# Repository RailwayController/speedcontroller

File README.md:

<!--
SPDX-FileCopyrightText: 2022 Sidings Media <contact@sidingsmedia.com>
SPDX-License-Identifier: CC-BY-SA-4.0
-->

# Railway Controller - Speed controller

The speed control board is one of the most important control nodes in the
railway controller system as it is responsible for powering the trains in use.

The board is based upon the ATtiny84 and makes use of the DRV8872 motor driver
IC. A small amount of protection circuitry to protect against large over
voltages on the motor lines has been included. The board is designed to fit
inside a standard 3U eurocard enclosure with a depth of 160mm and a height of
100mm. The rear connector provides connectivity to the backplane to allow
communication between all nodes in the rack as well as to supply power to the
board.

The PCBs have been designed with 2 layers and with SMD components that should be
possible to hand solder with a small tip and some practice. An important note,
the boards have been designed acording to JLCPCB's design constraints, if you
are ordering from a different manufacturer, it is a good idea to make sure that
they support the same or better constraints.

This repository contains designs for the speed control board for
use with the railway controller system. Rendered versions of the schematics, for
example schematics in the PDF format, are included with the releases. Gerber
files are also included with releases. These have been generated to work with
JLCPCB but they should work with most other board manufacturers. 

## Licence
This repo uses the [REUSE](https://reuse.software) standard in order to
communicate the correct licence for the file. For those unfamiliar with
the standard the licence for each file can be found in one of three
places. The licence will either be in a comment block at the top of the
file, in a `.license` file with the same name as the file, or in the
dep5 file located in the `.reuse` directory. If you are unsure of the
licencing terms please contact
[contact@sidingsmedia.com](mailto:contact@sidingsmedia.com?subject=Railway%20Controller%20Licence).
All files committed to this repo must contain valid licencing
information or the pull request can not be accepted.

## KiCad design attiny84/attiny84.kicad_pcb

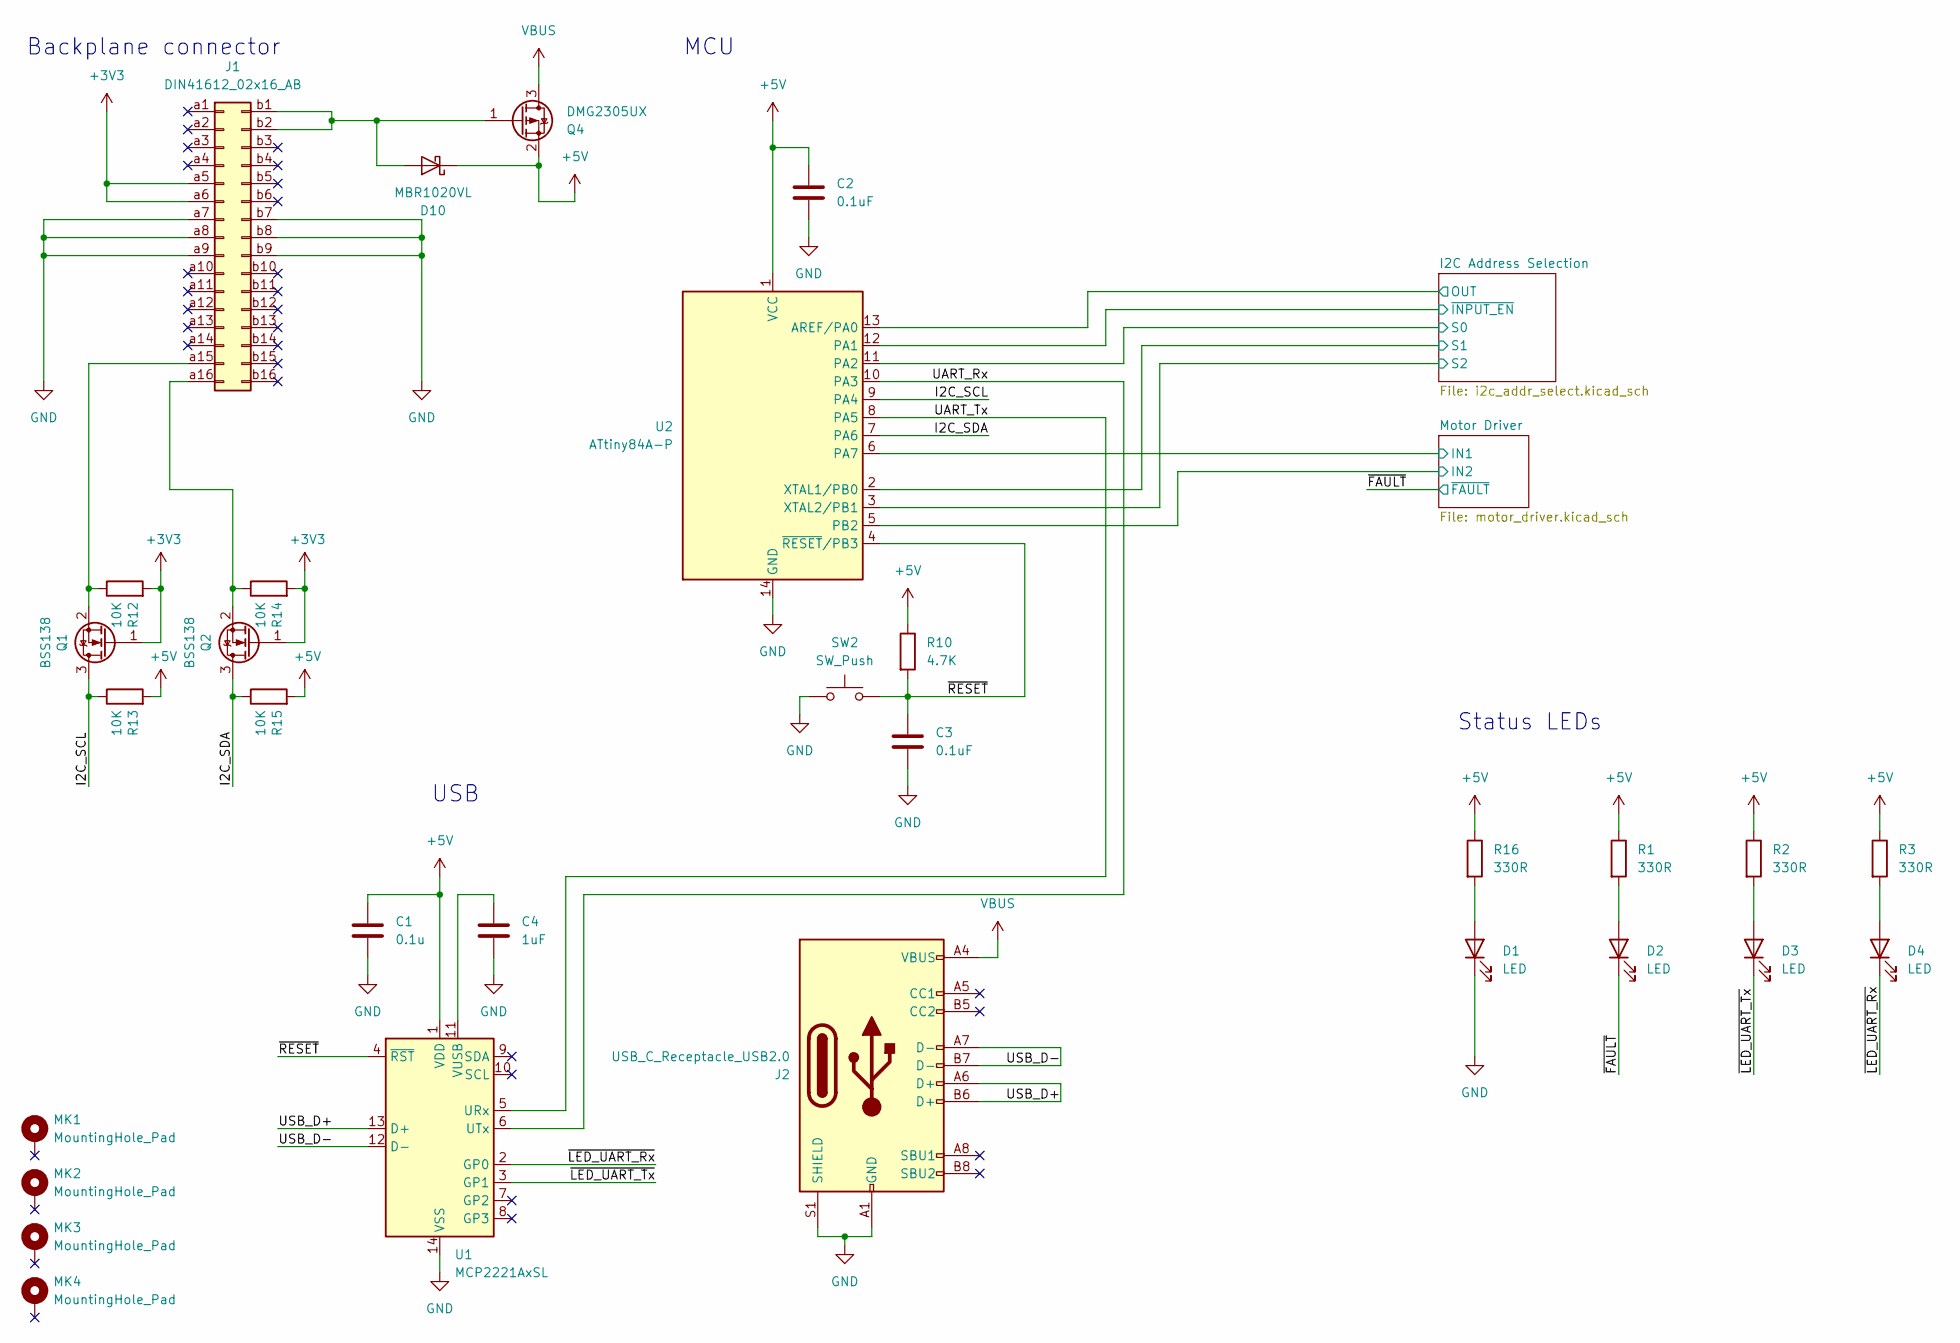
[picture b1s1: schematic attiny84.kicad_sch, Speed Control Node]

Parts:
C1: 0.1u; C_1206_3216Metric_Pad1.33x1.80mm_HandSolder
C2, C3: 0.1uF; C_1206_3216Metric_Pad1.33x1.80mm_HandSolder
C4: 1uF; C_1206_3216Metric_Pad1.33x1.80mm_HandSolder
D1, D2, D3, D4: LED; C_0402_1005Metric_Pad0.74x0.62mm_HandSolder
D10: MBR1020VL; D_SOD-123F
J1: DIN41612_02x16_AB; DIN41612_B2_2x16_Male_Horizontal_THT
J2: USB_C_Receptacle_USB2.0; USB_C_Receptacle_Palconn_UTC16-G
MK1, MK2, MK3, MK4: MountingHole_Pad; MountingHole_2.7mm
Q1, Q2: BSS138; SOT-23
Q4: DMG2305UX; SOT-23
R1, R2, R3, R16: 330R; R_1206_3216Metric_Pad1.30x1.75mm_HandSolder
R10: 4.7K; R_1206_3216Metric_Pad1.30x1.75mm_HandSolder
R12, R13, R14, R15: 10K; R_1206_3216Metric_Pad1.30x1.75mm_HandSolder
SW2: SW_Push; SW_SPST_B3U-1000P
U1: MCP2221AxSL; SOIC-14_3.9x8.7mm_P1.27mm
U2: ATtiny84A-P; SOIC-14_3.9x8.7mm_P1.27mm

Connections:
+3V3: J1.a5, J1.a6, Q1.1 (G), Q2.1 (G), R12.2, R14.2
+5V: C1.1, C2.1, D10.1 (K), Q4.2 (S), R1.1, R2.1, R3.1, R10.1, R13.2, R15.2, R16.1, U1.1 (VDD), U2.1 (VCC); also elsewhere on the board
/I2C Address Selection/OUT: U2.13 (AREF/PA0); also elsewhere on the board
/I2C Address Selection/S0: U2.11 (PA2); also elsewhere on the board
/I2C Address Selection/S1: U2.2 (XTAL1/PB0); also elsewhere on the board
/I2C Address Selection/S2: U2.3 (XTAL2/PB1); also elsewhere on the board
/I2C Address Selection/~INPUT_EN: U2.12 (PA1); also elsewhere on the board
/I2C_SCL: Q1.3 (D), R13.1, U2.9 (PA4)
/I2C_SDA: Q2.3 (D), R15.1, U2.7 (PA6)
/Motor Driver/IN1: U2.6 (PA7); also elsewhere on the board
/Motor Driver/IN2: U2.5 (PB2); also elsewhere on the board
/UART_Rx: U1.6 (UTx), U2.10 (PA3)
/UART_Tx: U1.5 (URx), U2.8 (PA5)
/USB_D+: J2.A6 (D+), J2.B6 (D+), U1.13 (D+)
/USB_D-: J2.A7 (D-), J2.B7 (D-), U1.12 (D-)
/~FAULT: D2.1 (K); also elsewhere on the board
/~LED_UART_Rx: D4.1 (K), U1.2 (GP0)
/~LED_UART_Tx: D3.1 (K), U1.3 (GP1)
/~RESET: C3.1, R10.2, SW2.2, U1.4 (~RST), U2.4 (~RESET/PB3)
GND: C1.2, C2.2, C3.2, C4.2, D1.1 (K), J1.a7, J1.a8, J1.a9, J1.b7, J1.b8, J1.b9, J2.A1 (GND), J2.A12 (GND), J2.B1 (GND), J2.B12 (GND), J2.S1 (SHIELD), SW2.1, U1.14 (VSS), U2.14 (GND); also elsewhere on the board
unnamed: C4.1, U1.11 (VUSB)
unnamed: D1.2 (A), R16.2
unnamed: D2.2 (A), R1.2
unnamed: D3.2 (A), R2.2
unnamed: D4.2 (A), R3.2
unnamed: D10.2 (A), J1.b1, J1.b2, Q4.1 (G)
unnamed: J1.a15, Q1.2 (S), R12.1
unnamed: J1.a16, Q2.2 (S), R14.1
VBUS: J2.A4 (VBUS), J2.A9 (VBUS), J2.B4 (VBUS), J2.B9 (VBUS), Q4.3 (D)

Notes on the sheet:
MCU
Backplane connector
Status LEDs
USB

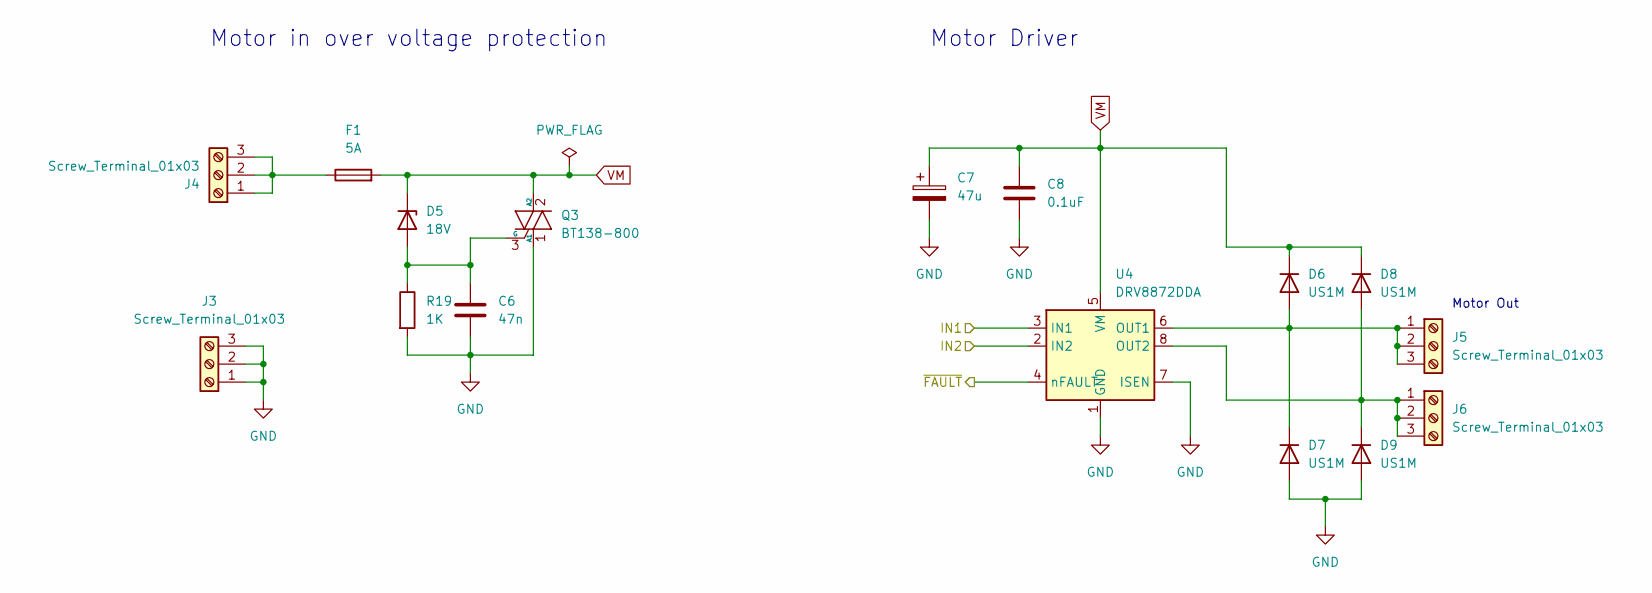
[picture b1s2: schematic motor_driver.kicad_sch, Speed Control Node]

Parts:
C6: 47n; C_1206_3216Metric_Pad1.33x1.80mm_HandSolder
C7: 47u; CP_Elec_6.3x5.7
C8: 0.1uF; C_1206_3216Metric_Pad1.33x1.80mm_HandSolder
D5: 18V; D_SOD-123F
D6, D7, D8, D9: US1M; D_SMA
F1: 5A; Fuseholder_Littelfuse_445_030_series_5x20mm
J3, J4, J5, J6: Screw_Terminal_01x03; TerminalBlock_bornier-3_P5.08mm
Q3: BT138-800; TO-220-3_Vertical
R19: 1K; R_1206_3216Metric_Pad1.30x1.75mm_HandSolder
U4: DRV8872DDA; Texas_HTSOP-8-1EP_3.9x4.9mm_P1.27mm_EP2.95x4.9mm_Mask2.4x3.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

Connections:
/Motor Driver/IN1: U4.3 (IN1); also elsewhere on the board
/Motor Driver/IN2: U4.2 (IN2); also elsewhere on the board
/~FAULT: U4.4 (nFAULT); also elsewhere on the board
GND: C6.2, C7.2, C8.2, D7.2 (A), D9.2 (A), J3.1, J3.2, J3.3, Q3.1 (A1), R19.2, U4.1 (GND), U4.7 (ISEN), U4.9 (GND); also elsewhere on the board
unnamed: C6.1, D5.2 (A), Q3.3 (G), R19.1
unnamed: D6.2 (A), D7.1 (K), J5.1, J5.2, J5.3, U4.6 (OUT1)
unnamed: D8.2 (A), D9.1 (K), J6.1, J6.2, J6.3, U4.8 (OUT2)
unnamed: F1.1, J4.1, J4.2, J4.3
VM: C7.1, C8.1, D5.1 (K), D6.1 (K), D8.1 (K), F1.2, Q3.2 (A2), U4.5 (VM)

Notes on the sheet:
Motor Driver
Motor Out
Motor in over voltage protection

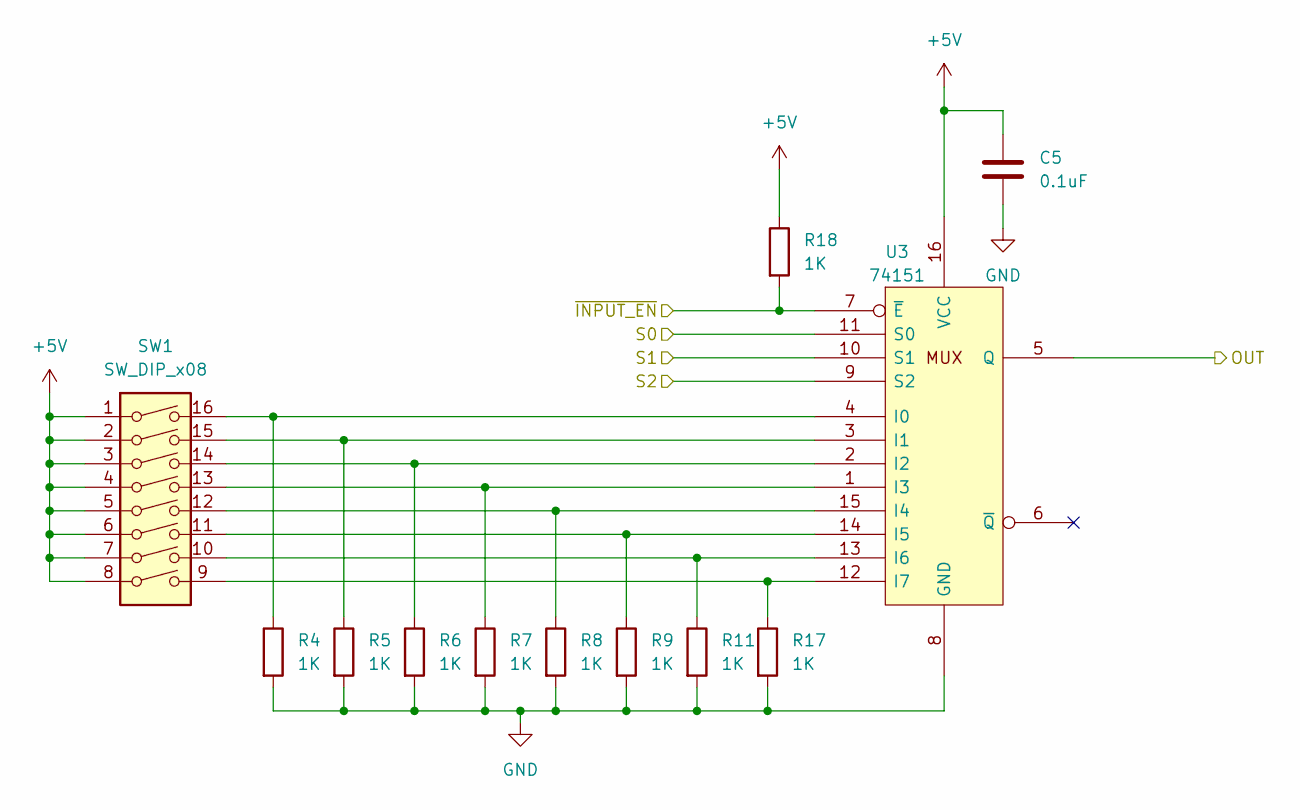
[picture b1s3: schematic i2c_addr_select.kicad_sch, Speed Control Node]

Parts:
C5: 0.1uF; C_1206_3216Metric_Pad1.33x1.80mm_HandSolder
R4, R5, R6, R7, R8, R9, R11, R17, R18: 1K; R_1206_3216Metric_Pad1.30x1.75mm_HandSolder
SW1: SW_DIP_x08; SW_DIP_SPSTx08_Slide_6.7x21.88mm_W7.62mm_P2.54mm_LowProfile
U3: 74151; SOIC-16_3.9x9.9mm_P1.27mm

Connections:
+5V: C5.1, R18.1, SW1.1, SW1.2, SW1.3, SW1.4, SW1.5, SW1.6, SW1.7, SW1.8, U3.16 (VCC); also elsewhere on the board
/I2C Address Selection/OUT: U3.5 (Q); also elsewhere on the board
/I2C Address Selection/S0: U3.11 (S0); also elsewhere on the board
/I2C Address Selection/S1: U3.10 (S1); also elsewhere on the board
/I2C Address Selection/S2: U3.9 (S2); also elsewhere on the board
/I2C Address Selection/~INPUT_EN: R18.2, U3.7 (~E); also elsewhere on the board
GND: C5.2, R4.2, R5.2, R6.2, R7.2, R8.2, R9.2, R11.2, R17.2, U3.8 (GND); also elsewhere on the board
unnamed: R4.1, SW1.16, U3.4 (I0)
unnamed: R5.1, SW1.15, U3.3 (I1)
unnamed: R6.1, SW1.14, U3.2 (I2)
unnamed: R7.1, SW1.13, U3.1 (I3)
unnamed: R8.1, SW1.12, U3.15 (I4)
unnamed: R9.1, SW1.11, U3.14 (I5)
unnamed: R11.1, SW1.10, U3.13 (I6)
unnamed: R17.1, SW1.9, U3.12 (I7)

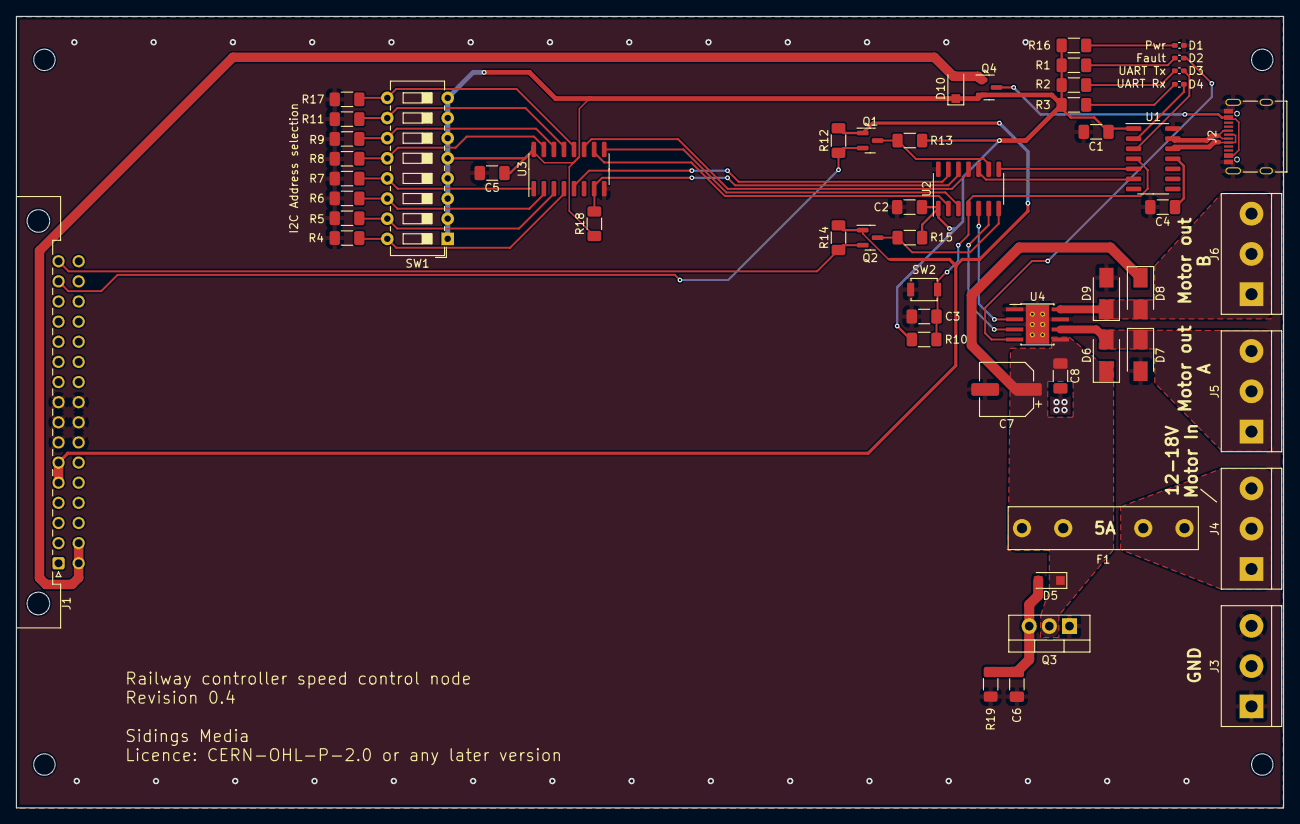
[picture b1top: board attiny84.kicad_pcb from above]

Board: 2 copper layers, 159.9 x 99.9 mm, 58 parts (0 on the bottom side), 42 nets.

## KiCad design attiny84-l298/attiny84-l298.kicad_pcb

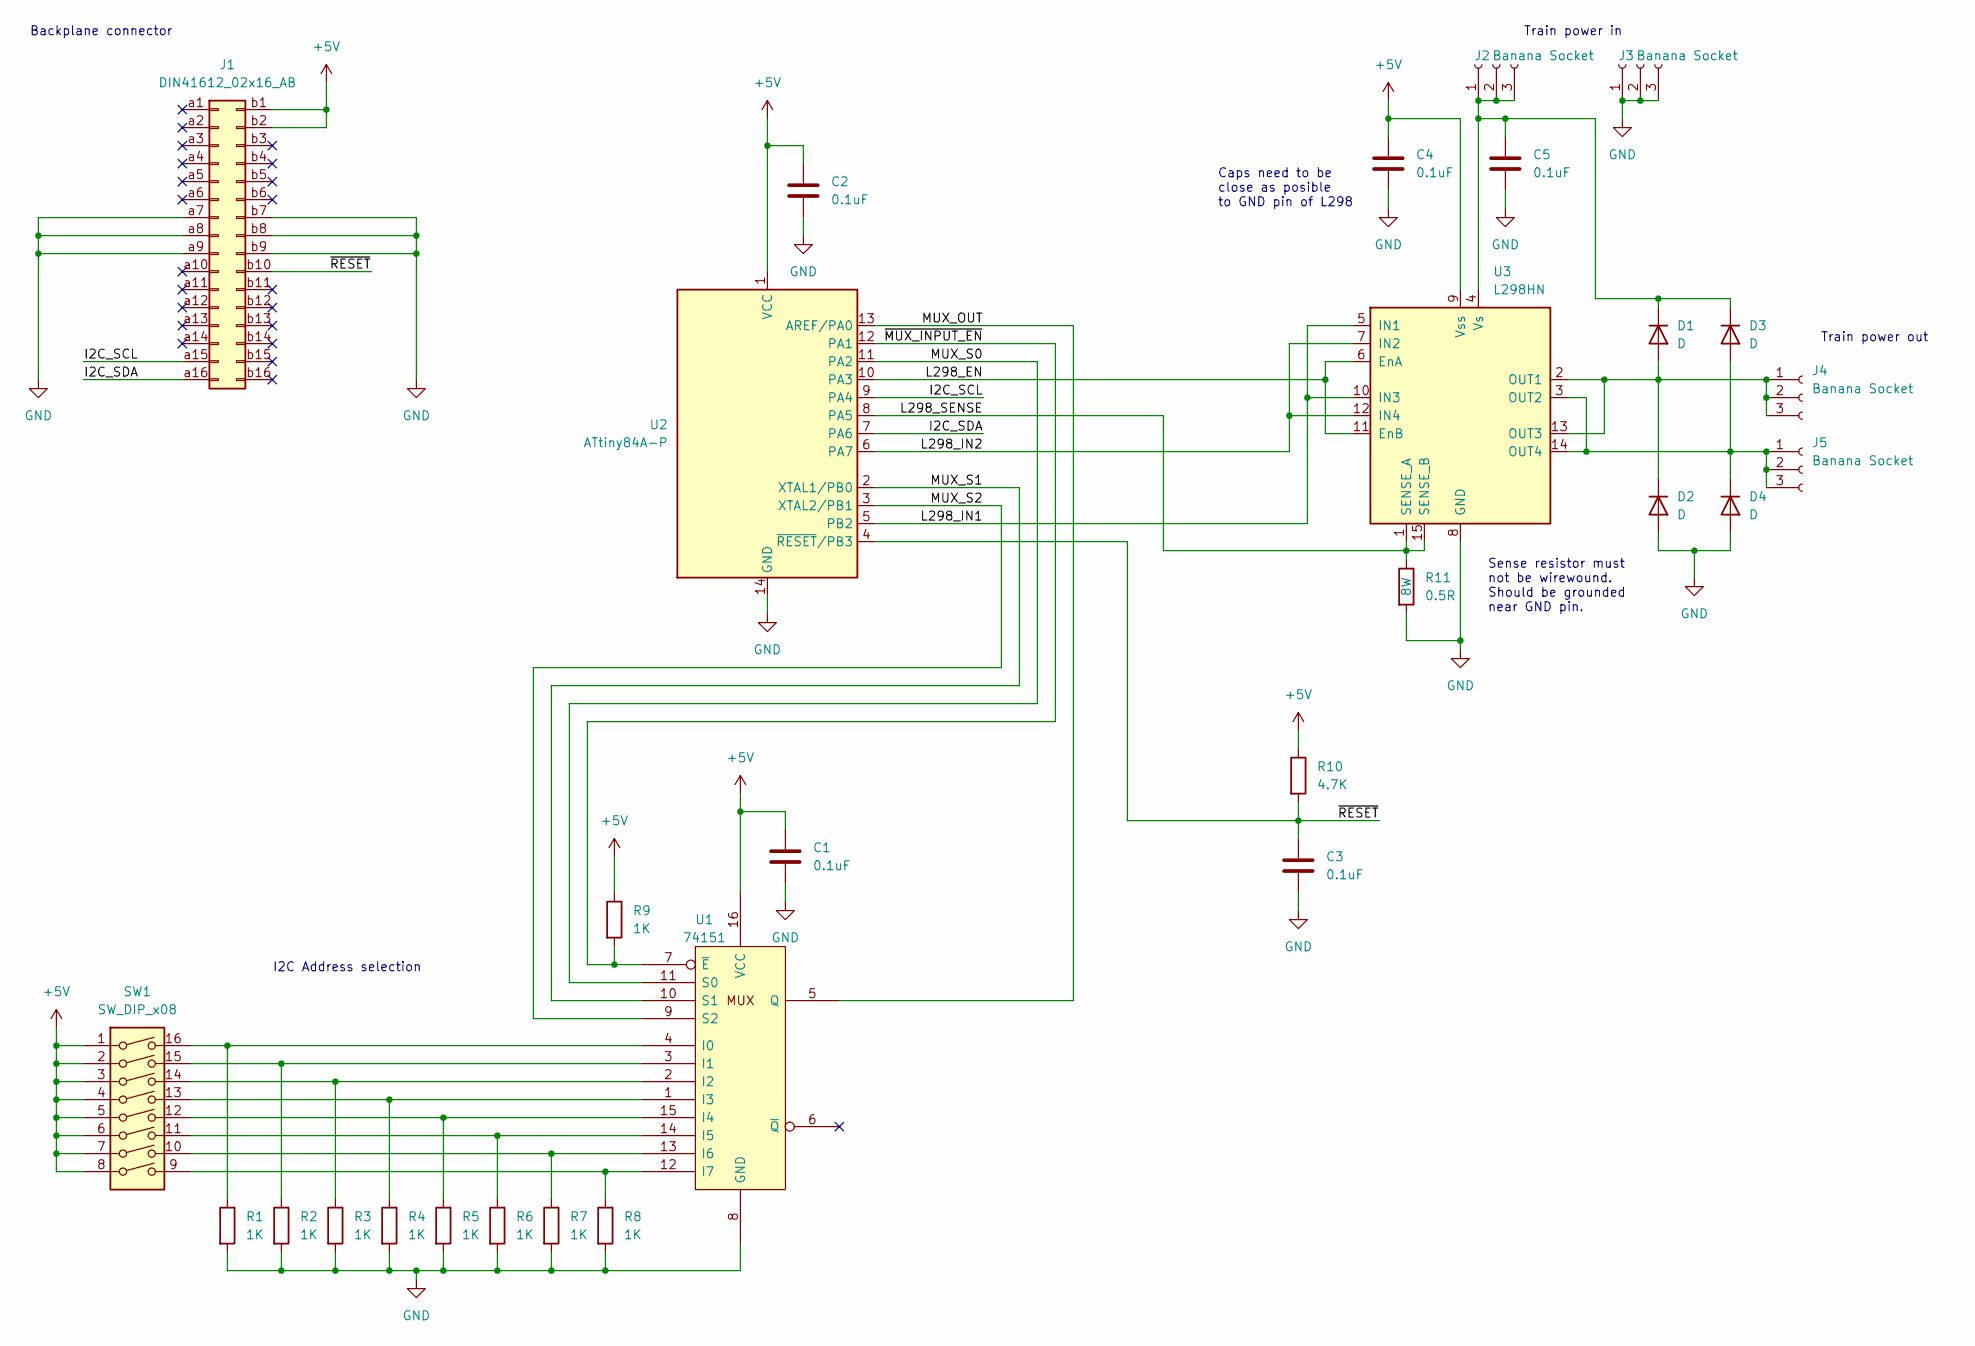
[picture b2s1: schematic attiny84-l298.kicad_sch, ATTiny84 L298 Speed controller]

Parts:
C1, C2, C3, C4, C5: 0.1uF; C_Disc_D4.7mm_W2.5mm_P5.00mm
D1, D2, D3, D4: D; D_5W_P10.16mm_Horizontal
J1: DIN41612_02x16_AB; DIN41612_B2_2x16_Male_Horizontal_THT
J2, J3, J4, J5: Banana Socket; Banana_Jack_3Pin
R1, R2, R3, R4, R5, R6, R7, R8, R9: 1K; R_Axial_DIN0207_L6.3mm_D2.5mm_P7.62mm_Horizontal
R10: 4.7K; R_Axial_DIN0207_L6.3mm_D2.5mm_P7.62mm_Horizontal
R11: 0.5R; R_Axial_DIN0617_L17.0mm_D6.0mm_P20.32mm_Horizontal
SW1: SW_DIP_x08; DIP-16_W7.62mm
U1: 74151; DIP-16_W7.62mm
U2: ATtiny84A-P; DIP-14_W7.62mm
U3: L298HN; TO-220-15_P2.54x2.54mm_StaggerOdd_Lead5.84mm_TabDown

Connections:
+5V: C1.1, C2.1, C4.1, J1.b1, J1.b2, R9.1, R10.1, SW1.1, SW1.2, SW1.3, SW1.4, SW1.5, SW1.6, SW1.7, SW1.8, U1.16 (VCC), U2.1 (VCC), U3.9 (Vss)
/I2C_SCL: J1.a15, U2.9 (PA4)
/I2C_SDA: J1.a16, U2.7 (PA6)
/L298_EN: U2.10 (PA3), U3.6 (EnA), U3.11 (EnB)
/L298_IN1: U2.5 (PB2), U3.5 (IN1), U3.10 (IN3)
/L298_IN2: U2.6 (PA7), U3.7 (IN2), U3.12 (IN4)
/L298_SENSE: R11.1, U2.8 (PA5), U3.1 (SENSE_A), U3.15 (SENSE_B)
/MUX_OUT: U1.5 (Q), U2.13 (AREF/PA0)
/MUX_S0: U1.11 (S0), U2.11 (PA2)
/MUX_S1: U1.10 (S1), U2.2 (XTAL1/PB0)
/MUX_S2: U1.9 (S2), U2.3 (XTAL2/PB1)
/~MUX_INPUT_EN: R9.2, U1.7 (~E), U2.12 (PA1)
/~RESET: C3.1, J1.b10, R10.2, U2.4 (~RESET/PB3)
GND: C1.2, C2.2, C3.2, C4.2, C5.2, D2.2 (A), D4.2 (A), J1.a7, J1.a8, J1.a9, J1.b7, J1.b8, J1.b9, J3.1, J3.2, J3.3, R1.2, R2.2, R3.2, R4.2, R5.2, R6.2, R7.2, R8.2, R11.2, U1.8 (GND), U2.14 (GND), U3.8 (GND)
unnamed: C5.1, D1.1 (K), D3.1 (K), J2.1, J2.2, J2.3, U3.4 (Vs)
unnamed: D1.2 (A), D2.1 (K), J4.1, J4.2, J4.3, U3.2 (OUT1), U3.13 (OUT3)
unnamed: D3.2 (A), D4.1 (K), J5.1, J5.2, J5.3, U3.3 (OUT2), U3.14 (OUT4)
unnamed: R1.1, SW1.16, U1.4 (I0)
unnamed: R2.1, SW1.15, U1.3 (I1)
unnamed: R3.1, SW1.14, U1.2 (I2)
unnamed: R4.1, SW1.13, U1.1 (I3)
unnamed: R5.1, SW1.12, U1.15 (I4)
unnamed: R6.1, SW1.11, U1.14 (I5)
unnamed: R7.1, SW1.10, U1.13 (I6)
unnamed: R8.1, SW1.9, U1.12 (I7)

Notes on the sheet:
Sense resistor must not be wirewound. Should be grounded near GND pin.
I2C Address selection
Caps need to be close as posible to GND pin of L298
Backplane connector
Train power out
Train power in

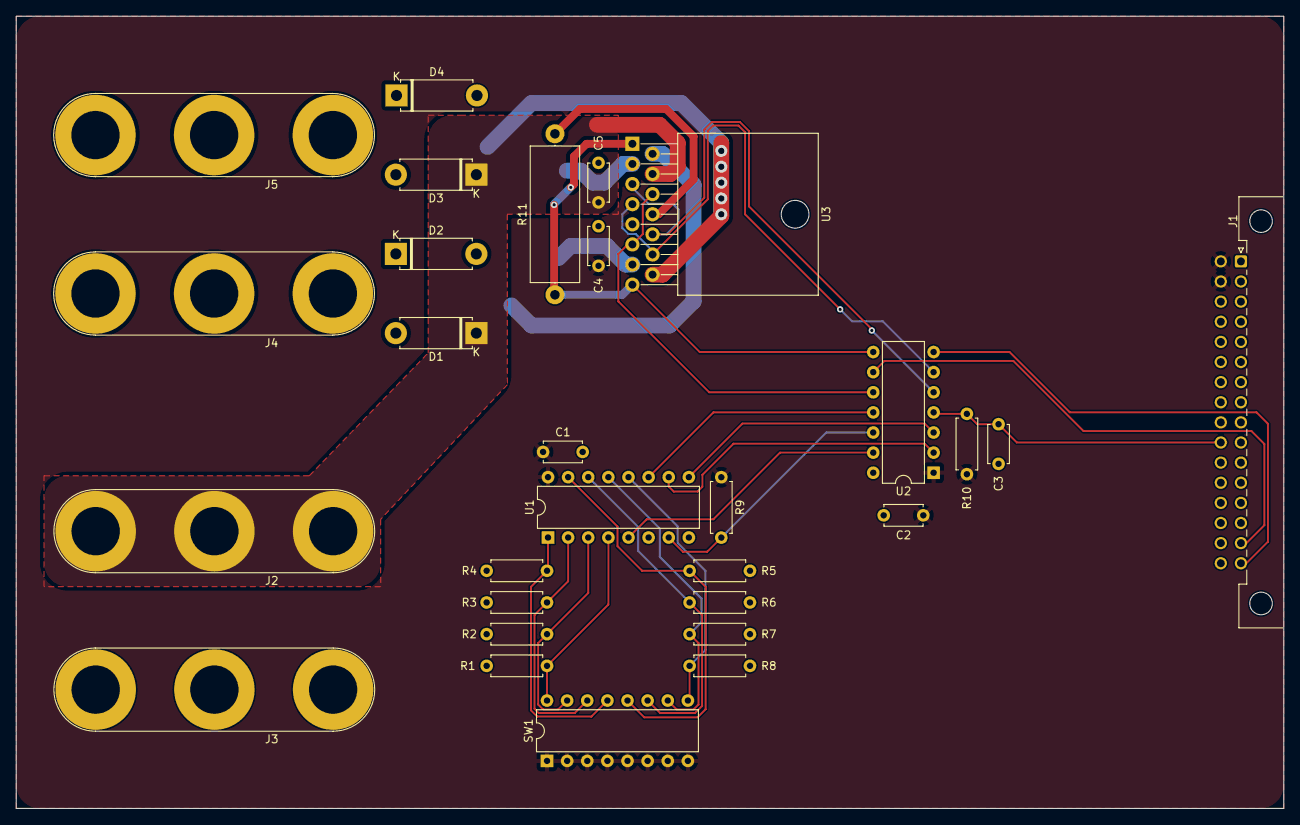
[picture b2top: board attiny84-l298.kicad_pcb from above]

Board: 2 copper layers, 160.0 x 100.0 mm, 29 parts (0 on the bottom side), 25 nets.

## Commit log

2022-09-16 Updated readme with correct info
2022-09-16 Added basic templates
2022-09-16 Created kicad project
2022-09-16 attiny84-l298 V0.1 Schematic
2022-09-16 Assigned footprints for attiny84-l298
2022-09-17 Fixed net label name
2022-09-17 V0.1 of attiny84-l298
2022-09-17 Cleaned up schematic and fixed DRC errors
2022-09-17 Added PDF of schematic and interactive BOM
2022-11-26 Updated .gitignore with production files
2022-11-26 Restructured project + changed motor driver IC
    The motor driver IC has been changed from the L298N to the DRV8872 due
    to it's smaller size, improved efficiency, lower cost and it's
    requirement for fewer external components. The banana plugs have also
    been removed in favour of screw terminals. A USB interface has also been
    added to allow for firmware to be updated by the end user. Additional
    LEDs have been added to indicate USB traffic and motor driver faults.
2022-11-26 Removed old files
2022-11-26 Fixed reuse compliance
2022-11-26 Assigned footprints to all components
2022-11-26 Changed hole refference to match other schematics
2022-11-26 Removed left over net label from IN1
2022-11-26 Updated footprint of dip switch
    The footprint of SW1 has been changed from a generic DIP package to a
    specific DIP switch.
2022-11-26 Designed PCB for rev 0.3
    The PCB has been designed for rev 0.3 of the circuit.
2022-11-27 Updated README to include image + more detail
2022-11-27 Updated settings for gerber export
2022-12-20 Removed reset pin on backplane
    The connection between the reset pin and the backplane has been removed
    as it is not required. The reset pin on the backplane served no function
    as it would be near impossible to use in practice and was likely to
    cause issues surrounding pullup resistors if too many boards were added.
    As such, the link between the backplane and the IC reset pins has been
    removed, leaving only the reset button on the board.
2022-12-20 Fixed revision + terminology on silk screen

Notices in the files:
attiny84-l298/attiny84-l298.kicad_pcb:
Licence: CERN-OHL-P-2.0 or any later version
